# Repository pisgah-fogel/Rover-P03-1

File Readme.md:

# Rover as a development platform for Soft CPUs (real time application)

# Boogie Chassis

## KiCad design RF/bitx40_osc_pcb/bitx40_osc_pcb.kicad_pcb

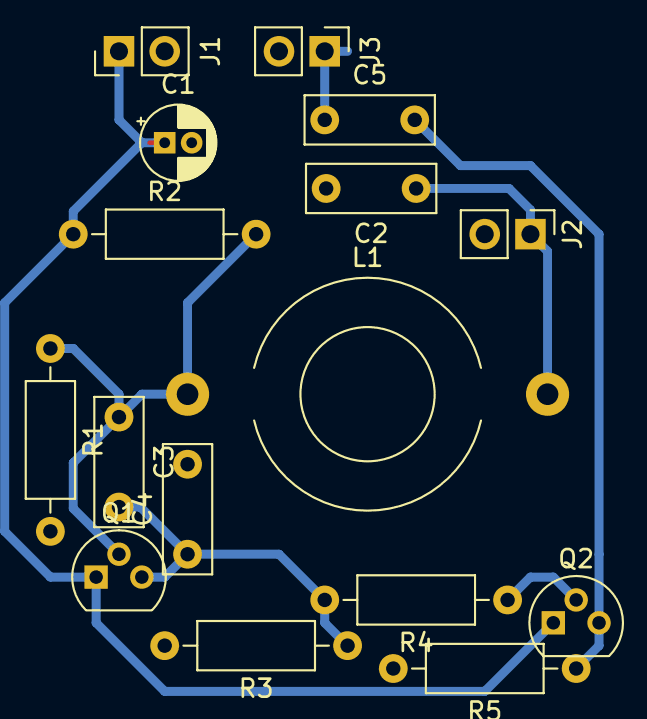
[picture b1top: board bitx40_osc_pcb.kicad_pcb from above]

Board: 2 copper layers, 16 parts (0 on the bottom side), 8 nets.

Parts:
C1: 0.1 uF; CP_Radial_D4.0mm_P1.50mm
C2: 120 pF; C_Disc_D7.0mm_W2.5mm_P5.00mm
C3, C4: 1000 pF; C_Disc_D7.0mm_W2.5mm_P5.00mm
C5: 0.1 uF; C_Disc_D7.0mm_W2.5mm_P5.00mm
J1: Alim 5V; PinHeader_1x02_P2.54mm_Vertical
J2: Variable Capacitor; PinHeader_1x02_P2.54mm_Vertical
J3: Oscillator Output; PinHeader_1x02_P2.54mm_Vertical
L1: 9 uH; L_Toroid_Horizontal_D12.7mm_P20.00mm_Diameter14-5mm_Amidon-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
Q1, Q2: 2N3904; TO-92
R1, R2, R4: 10k; R_Axial_DIN0207_L6.3mm_D2.5mm_P10.16mm_Horizontal
R3: 2.2k; R_Axial_DIN0207_L6.3mm_D2.5mm_P10.16mm_Horizontal
R5: 1k; R_Axial_DIN0207_L6.3mm_D2.5mm_P10.16mm_Horizontal

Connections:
+5V: C1.1, J1.1, Q1.1, Q2.1, R2.1
GND: C1.2, C2.2, C4.2, J1.2, J2.2, J3.2, R1.2, R3.2, R5.2
unnamed: C2.1, J2.1, L1.2
unnamed: C3.1, L1.1, Q1.2, R1.1, R2.2
unnamed: C3.2, C4.1, Q1.3, R3.1, R4.2
unnamed: C5.1, J3.1
unnamed: C5.2, Q2.3, R5.1
unnamed: Q2.2, R4.1

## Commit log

2019-04-15 3D models of FPGA (AX309 and Altera) + blank body
2019-04-15 Ameliorer le chassis et servo MG996R (Modele roue vide)
2019-05-04 Work on Bitx40 RF 7MHz (40m) Clapp oscillator
    Qucs simulation ok (but weird)
    Fritzing schematic (not recommanded for PCB but Ok for prototyping)
    Kicad schematic + PCB (verified OK)
2019-05-05 Correct 2N3904 package & review (ok)
2019-07-21 WIP Bitx40 prototype and merge 3D designs
2019-07-23 Add a Readme
    Create a markdown readme file to describe the current (WIP) project's
    status.
2019-11-17 Add complete rover 3D model
2019-11-17 Add DC H bridge support
2019-11-26 Add rover model for 3d printing
2019-11-26 Resize the power board box (++height)
2019-11-26 Change screw orientation (no nuts needed anymore)
2019-11-26 Add place for screw and small improvments
2019-11-27 Create Wheel
2019-11-27 Make box support easier to print
2019-11-27 Add information about raspberry pi
2019-11-27 Remove no usefull
2019-11-27 Remove useless files
2019-11-27 Add readme
2019-11-28 Wheel: Support DC ok + Wheel ok
2019-11-28 Remove unecessary 3D design
2019-11-28 Rename rover to ROver
2019-11-28 WIP Boogie
2019-11-28 WIP raspberri 0W box
2019-11-29 Passed, test Servo SG90
2019-11-29 Add experiements results
2019-11-29 Bottom tested raspberry case
2019-11-29 Tested, Boogie base OK
2019-11-29 Create .gitignore for useless Freecad products
2020-09-06 Immprove Robustness (To be tested)
2020-09-07 Test TFT display
2020-09-07 TFT schematic
2020-11-03 Pynq Z2 Reference
2020-11-03 Printing 1
2020-11-03 Correction des joints trop flottants: a imprimer
2020-11-03 WIP Shafts test 1
2020-11-04 Small adjustments
2020-11-05 Ajout 'grosse rondelle'
2020-11-05 Alternative to screw and small adjustment
2020-11-05 Add images and readme
2021-01-13 Test stepper motor
2021-01-18 Add acceleration
2021-01-19 test 3 different nema17 motors
2021-01-20 earth rotation compensation Ok, 400mA at 12V with the 1:139 NEMA motor
    Motor reference Hanpose 17HS4401S-PG139
2021-01-20 Move directories around
2021-01-22 Temperature and humidity plot
2021-01-22 WIP real time graph and B&W camera
2021-01-22 static results ok
2021-01-23 WIP cleanup
2021-01-23 Detect correct number of stars in simulation
2021-01-23 WIP graph of star's x position doesn't work
2021-01-24 detectstarx movement
2021-01-24 Failed with real webcam (not enough sensitivity)
2021-03-02 WIP Writting program to debug Astro mount's tracking
